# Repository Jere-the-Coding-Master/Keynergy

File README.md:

# Keynergy PCB Design
Solenoid Keys circuit connection design

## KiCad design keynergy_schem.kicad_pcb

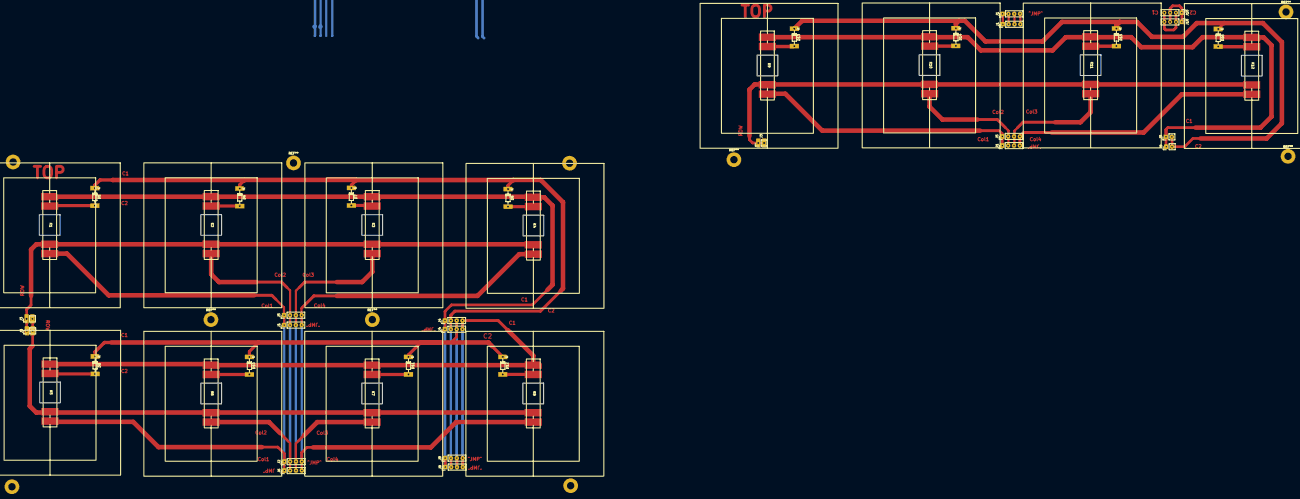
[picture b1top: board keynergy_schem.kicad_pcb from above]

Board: 2 copper layers, 43 parts (0 on the bottom side), 23 nets.

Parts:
D5, D6, D7, D8, D9, D10, D11, D12, D13, D14, D15, D16: 1N4001; D_DO-34_SOD68_P7.62mm_Horizontal
J1, J1#2, J1#3, J1#4, J2, J4, J4#2, J5, J5#2, J6, J8, J8#2, J10, J10#2: Conn_01x04_Pin; PinHeader_1x04_P2.54mm_Vertical
J3, J3#2, J3#3, J9, J9#2: Conn_01x02_Pin; PinHeader_1x02_P2.54mm_Vertical
K1, K2, K3, K4, K5, K6, K7, K8, K9, K10, K11, K12: Solenoid Key

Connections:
Coil 1-1: J4.1, J4#2.1, J8.1, J8#2.1, K1.1 (C1), K2.1 (C1), K3.1 (C1), K4.1 (C1)
Coil 1-2: D5.1 (K), D6.1 (K), D7.1 (K), D8.1 (K), J4.2, J4#2.2, J8.2, J8#2.2
Coil 2-1: J4.4, J4#2.4, J8.4, J8#2.4, J9.1, J9#2.1, J10.2, J10.4, J10#2.2, J10#2.4, K5.1 (C1), K6.1 (C1), K7.1 (C1), K8.1 (C1), K9.1 (C1), K10.1 (C1), K11.1 (C1), K12.1 (C1)
Coil 2-2: D9.1 (K), D10.1 (K), D11.1 (K), D12.1 (K), D13.1 (K), D14.1 (K), D15.1 (K), D16.1 (K), J4.3, J4#2.3, J8.3, J8#2.3, J9.2, J9#2.2, J10.1, J10.3, J10#2.1, J10#2.3
Column 1: J1.1, J1#2.1, J1#3.1, J1#4.1, J2.1, J5.1, J5#2.1, J6.1, K1.4 (Bin), K5.4 (Bin), K9.4 (Bin)
Column 2: J1.2, J1#2.2, J1#3.2, J1#4.2, J2.2, J5.2, J5#2.2, J6.2, K2.4 (Bin), K6.4 (Bin), K10.4 (Bin)
Column 3: J1.3, J1#2.3, J1#3.3, J1#4.3, J2.3, J5.3, J5#2.3, J6.3, K3.4 (Bin), K7.4 (Bin), K11.4 (Bin)
Column 4: J1.4, J1#2.4, J1#3.4, J1#4.4, J2.4, J5.4, J5#2.4, J6.4, K4.4 (Bin), K8.4 (Bin), K12.4 (Bin)
unnamed: D5.2 (A), K1.2 (C2)
unnamed: D6.2 (A), K2.2 (C2)
unnamed: D7.2 (A), K3.2 (C2)
unnamed: D8.2 (A), K4.2 (C2)
unnamed: D9.2 (A), K5.2 (C2)
unnamed: D10.2 (A), K6.2 (C2)
unnamed: D11.2 (A), K7.2 (C2)
unnamed: D12.2 (A), K8.2 (C2)
unnamed: D13.2 (A), K9.2 (C2)
unnamed: D14.2 (A), K10.2 (C2)
unnamed: D15.2 (A), K11.2 (C2)
unnamed: D16.2 (A), K12.2 (C2)
Row 1: J3.1, J3#2.1, J3#3.1, K1.3 (Bout), K2.3 (Bout), K3.3 (Bout), K4.3 (Bout)
Row 2: J3.2, J3#2.2, J3#3.2, K5.3 (Bout), K6.3 (Bout), K7.3 (Bout), K8.3 (Bout)
Row 3: K9.3 (Bout), K10.3 (Bout), K11.3 (Bout), K12.3 (Bout)

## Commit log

2025-03-28 new files
2025-03-29 new updates
2025-03-30 new update
2025-03-31 custom selonoid key added
2025-04-23 new updates, pdf exported
